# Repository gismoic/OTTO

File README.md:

# OTTO

A MP3 Player design I came up with about a year ago, the theroy behind it's design works as the following. The STM32C031C6T6 would interface the SD card through an SPI, stream Encodded audio data to the microcontroller, there it would be decoded into PCM samples, those samples would then be streamed to the LM49450, there it would be converted into analog audio signals which will be sent to speakers.

This project has no real hardware prototype but the design is here and can be revised if I ever feel like returning to this project. The firmware folder holds a software prototype for MP3 decodeding. A project that has proven to be very difficult. I would like to come back to this project in the future and come at with some new ideas. However, due to the fact that testing hardware like this would be very costly and difficult for me at the moment, I can not continue this project, but all the project files are in this repository for better storage in the future.

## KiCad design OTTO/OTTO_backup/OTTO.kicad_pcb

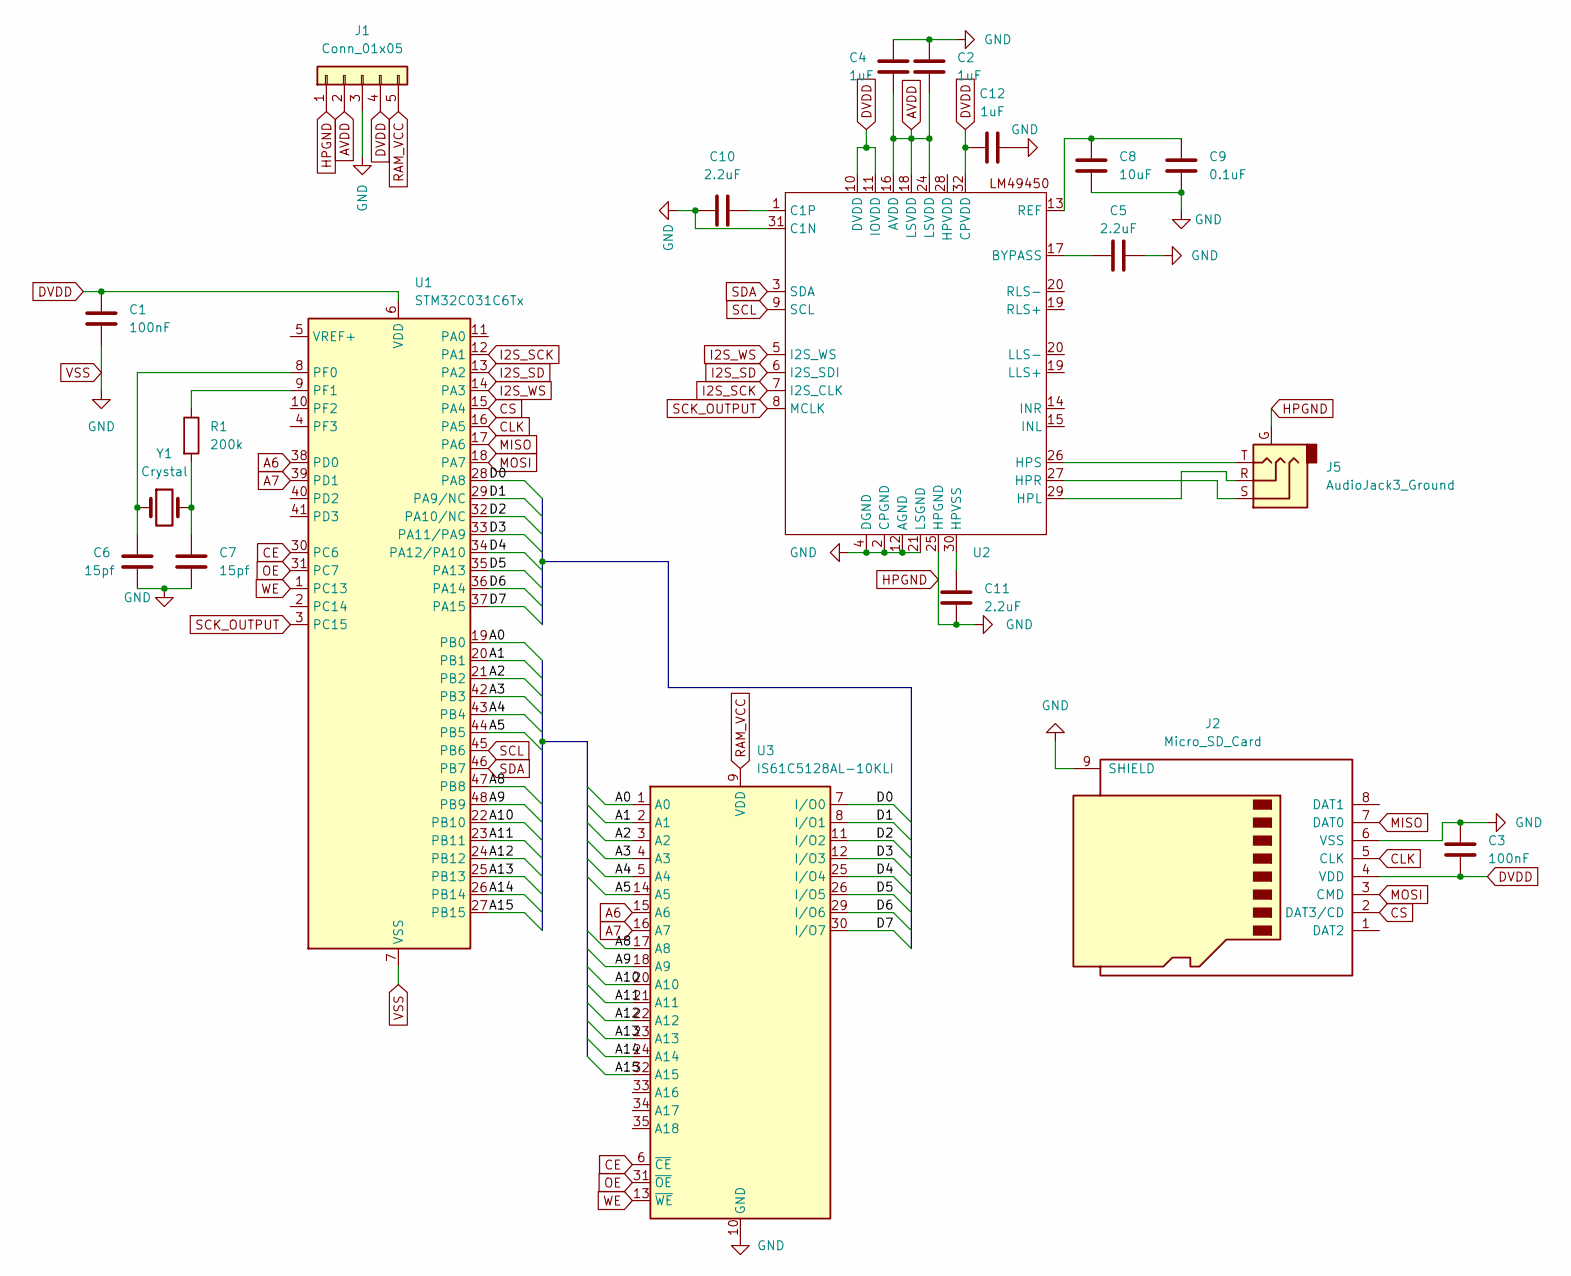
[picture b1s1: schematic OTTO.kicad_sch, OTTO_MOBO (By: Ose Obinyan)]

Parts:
C1, C3: 100nF; C_0201_0603Metric_Pad0.64x0.40mm_HandSolder
C2, C4, C12: 1uF; C_0201_0603Metric_Pad0.64x0.40mm_HandSolder
C5, C10, C11: 2.2uF; C_0201_0603Metric_Pad0.64x0.40mm_HandSolder
C6, C7: 15pf; C_0201_0603Metric_Pad0.64x0.40mm_HandSolder
C8: 10uF; C_0201_0603Metric_Pad0.64x0.40mm_HandSolder
C9: 0.1uF; C_0201_0603Metric_Pad0.64x0.40mm_HandSolder
J1: Conn_01x05; PinHeader_1x05_P1.00mm_Vertical
J2: Micro_SD_Card; microSD_HC_Hirose_DM3D-SF
J5: AudioJack3_Ground; Jack_3.5mm_CUI_SJ2-3593D-SMT_Horizontal
R1: 200k; R_0201_0603Metric_Pad0.64x0.40mm_HandSolder
U1: STM32C031C6Tx; LQFP-48_7x7mm_P0.5mm
U2: WQFN-32-1EP_5x5mm_P0.5mm_EP3.1x3.1mm
U3: IS61C5128AL-10KLI; SOJ-36_10.16x23.49mm_P1.27mm
Y1: Crystal; Crystal_SMD_EuroQuartz_MJ-4Pin_5.0x3.2mm_HandSoldering

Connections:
/A0: U1.19 (PB0), U3.1 (A0)
/A1: U1.20 (PB1), U3.2 (A1)
/A2: U1.21 (PB2), U3.3 (A2)
/A3: U1.42 (PB3), U3.4 (A3)
/A4: U1.43 (PB4), U3.5 (A4)
/A5: U1.44 (PB5), U3.14 (A5)
/A8: U1.47 (PB8), U3.17 (A8)
/A9: U1.48 (PB9), U3.18 (A9)
/A10: U1.22 (PB10), U3.20 (A10)
/A11: U1.23 (PB11), U3.21 (A11)
/A12: U1.24 (PB12), U3.22 (A12)
/A13: U1.25 (PB13), U3.23 (A13)
/A14: U1.26 (PB14), U3.24 (A14)
/A15: U1.27 (PB15), U3.32 (A15)
/D0: U1.28 (PA8), U3.7 (I/O0)
/D1: U1.29 (PA9/NC), U3.8 (I/O1)
/D2: U1.32 (PA10/NC), U3.11 (I/O2)
/D3: U1.33 (PA11/PA9), U3.12 (I/O3)
/D4: U1.34 (PA12/PA10), U3.25 (I/O4)
/D5: U1.35 (PA13), U3.26 (I/O5)
/D6: U1.36 (PA14), U3.29 (I/O6)
/D7: U1.37 (PA15), U3.30 (I/O7)
A6: U1.38 (PD0), U3.15 (A6)
A7: U1.39 (PD1), U3.16 (A7)
AVDD: C2.2, C4.2, J1.2, U2.16 (AVDD), U2.18 (LSVDD), U2.24 (LSVDD)
CE: U1.30 (PC6), U3.6 (~CE)
CLK: J2.5 (CLK), U1.16 (PA5)
CS: J2.2 (DAT3/CD), U1.15 (PA4)
DVDD: C1.1, C3.2, C12.1, J1.4, J2.4 (VDD), U1.6 (VDD), U2.10 (DVDD), U2.11 (IOVDD), U2.32 (CPVDD)
HPGND: C1.2, C2.1, C3.1, C4.1, C5.2, C6.2, C7.2, C8.1, C9.1, C10.1, C11.1, C12.2, J1.1, J1.3, J2.6 (VSS), J2.9 (SHIELD), J5.G, U1.7 (VSS), U2.2 (CPGND), U2.4 (DGND), U2.12 (AGND), U2.21 (LSGND), U2.25 (HPGND), U2.31 (C1N), U3.10 (GND), U3.28 (GND)
I2S_SCK: U1.12 (PA1), U2.7 (I2S_CLK)
I2S_SD: U1.13 (PA2), U2.6 (I2S_SDI)
I2S_WS: U1.14 (PA3), U2.5 (I2S_WS)
MISO: J2.7 (DAT0), U1.17 (PA6)
MOSI: J2.3 (CMD), U1.18 (PA7)
unnamed: C7.1, R1.2, Y1.2
unnamed: C6.1, U1.8 (PF0), Y1.1
unnamed: R1.1, U1.9 (PF1)
unnamed: C5.1, U2.17 (BYPASS)
unnamed: C10.2, U2.1 (C1P)
unnamed: J5.R, U2.29 (HPL)
unnamed: J5.S, U2.27 (HPR)
unnamed: J5.T, U2.26 (HPS)
unnamed: C11.2, U2.30 (HPVSS)
unnamed: C8.2, C9.2, U2.13 (REF)
OE: U1.31 (PC7), U3.31 (~OE)
RAM_VCC: J1.5, U3.9 (VDD), U3.27 (VDD)
SCK_OUTPUT: U1.3 (PC15), U2.8 (MCLK)
SCL: U1.45 (PB6), U2.9 (SCL)
SDA: U1.46 (PB7), U2.3 (SDA)
WE: U1.1 (PC13), U3.13 (~WE)

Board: 2 copper layers, 20 parts (0 on the bottom side), 51 nets, no tracks yet.

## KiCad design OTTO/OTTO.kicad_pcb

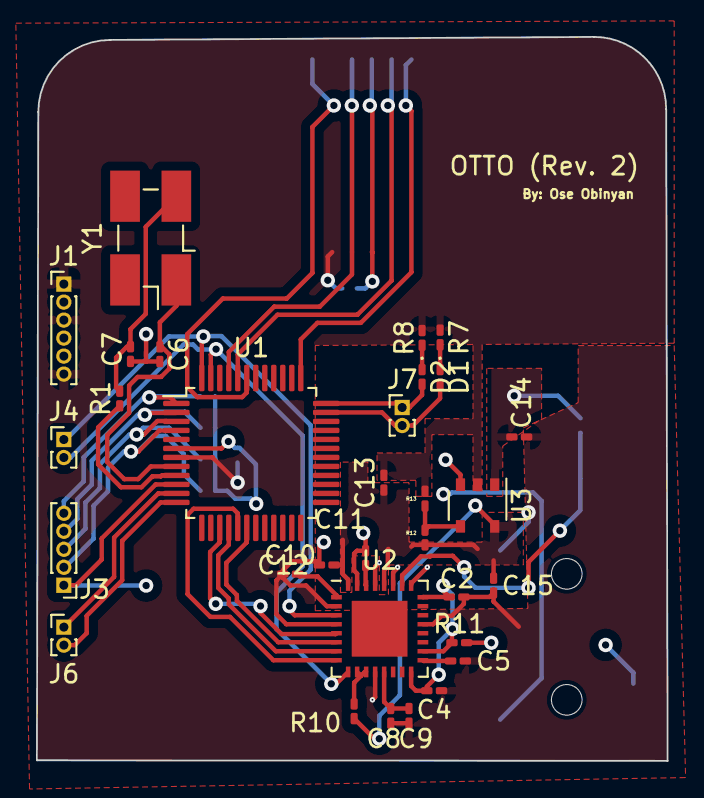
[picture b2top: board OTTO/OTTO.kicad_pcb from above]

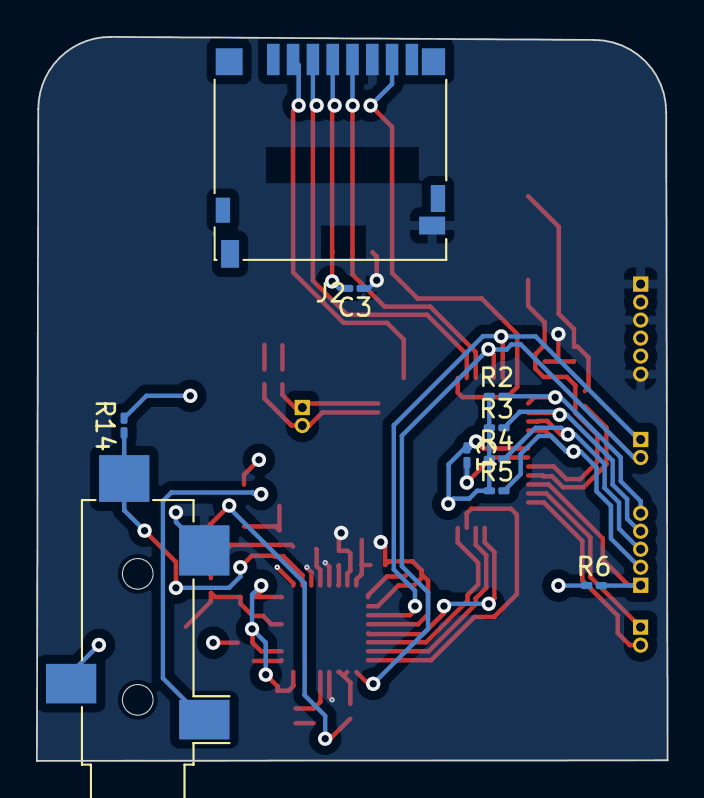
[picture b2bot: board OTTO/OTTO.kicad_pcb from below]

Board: 4 copper layers, 35.0 x 40.2 mm, 41 parts (10 on the bottom side), 37 nets.

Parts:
C1, C3: 100nF; C_0201_0603Metric_Pad0.64x0.40mm_HandSolder
C2, C4, C12, C13, C14: 1uF; C_0201_0603Metric_Pad0.64x0.40mm_HandSolder
C5, C10, C11: 2.2uF; C_0201_0603Metric_Pad0.64x0.40mm_HandSolder
C6, C7: 15pf; C_0201_0603Metric_Pad0.64x0.40mm_HandSolder
C8: 10uF; C_0201_0603Metric_Pad0.64x0.40mm_HandSolder
C9: 0.1uF; C_0201_0603Metric_Pad0.64x0.40mm_HandSolder
C15: 0.7uF; C_0201_0603Metric_Pad0.64x0.40mm_HandSolder
D1, D2: LED; LED_0201_0603Metric_Pad0.64x0.40mm_HandSolder
J1: Conn_01x05; PinHeader_1x06_P1.00mm_Vertical
J2: Micro_SD_Card; microSD_HC_Hirose_DM3D-SF
J3: Conn_01x05; PinHeader_1x05_P1.00mm_Vertical
J4, J6, J7: Conn_01x02; PinHeader_1x02_P1.00mm_Vertical
J5: AudioJack3_SwitchT; Jack_3.5mm_CUI_SJ-3524-SMT_Horizontal
R1: 200k; R_0201_0603Metric_Pad0.64x0.40mm_HandSolder
R2, R3, R4, R5, R6, R7, R8, R14: 1k; R_0201_0603Metric_Pad0.64x0.40mm_HandSolder
R10, R11: 300; R_0201_0603Metric_Pad0.64x0.40mm_HandSolder
R12: 500; R_0201_0603Metric_Pad0.64x0.40mm_HandSolder
R13: 357; R_0201_0603Metric_Pad0.64x0.40mm_HandSolder
U1: STM32C031C6Tx; LQFP-48_7x7mm_P0.5mm
U2: WQFN-32-1EP_5x5mm_P0.5mm_EP3.1x3.1mm
U3: TSOP-5_1.65x3.05mm_P0.95mm
Y1: Crystal; Crystal_SMD_EuroQuartz_MJ-4Pin_5.0x3.2mm_HandSoldering

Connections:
2.7v: C12.1, C13.1, C15.2, R10.2, R12.1, U2.28 (HPVDD), U2.32 (CPVDD), U3.5 (VOUT)
3.3v: C1.1, C3.2, C14.2, J1.4, J2.4 (VDD), R2.1, R3.1, R4.1, R5.1, R6.1, R11.2, R14.2, U1.6 (VDD), U3.1 (VIN), U3.3 (EN)
.: J3.5, R2.2, U1.1 (PC13)
..: J3.4, R3.2, U1.2 (PC14)
...: J3.3, R4.2, U1.3 (PC15)
....: J3.2, R5.2, U1.4 (PF3)
CLK: J2.5 (CLK), U1.45 (PB6)
CS: J2.2 (DAT3/CD), U1.37 (PA15)
Enter: J3.1, R6.2, U1.10 (PF2)
HPL: J5.S, U2.29 (HPL)
HPR: J5.R, U2.27 (HPR)
HPS: J5.TN, R14.1, U2.26 (HPS)
I2S_MCK: U1.17 (PA6), U2.8 (MCLK)
I2S_SCK: U1.16 (PA5), U2.7 (I2S_CLK)
I2S_SD: U1.18 (PA7), U2.6 (I2S_SDI)
I2S_WS: U1.15 (PA4), U2.5 (I2S_WS)
MISO: J2.7 (DAT0), U1.43 (PB4)
MOSI: J2.3 (CMD), U1.44 (PB5)
unnamed: C7.1, R1.2, Y1.2
unnamed: D1.1 (K), R7.2
unnamed: D2.1 (K), R8.2
unnamed: C6.1, U1.8 (PF0), Y1.1
unnamed: R1.1, U1.9 (PF1)
unnamed: C2.2, C4.2, R11.1, U2.16 (AVDD), U2.18 (LSVDD), U2.24 (LSVDD)
unnamed: C5.1, U2.17 (BYPASS)
unnamed: C10.2, U2.1 (C1P)
unnamed: R10.1, U2.10 (DVDD), U2.11 (IOVDD)
unnamed: C11.2, U2.30 (HPVSS)
unnamed: C8.2, C9.2, U2.13 (REF)
unnamed: R12.2, R13.1, U3.4 (ADJ)
RX: J6.2, U1.12 (PA1)
SCL: J4.2, U1.47 (PB8), U2.9 (SCL)
SDA: J4.1, U1.48 (PB9), U2.3 (SDA)
SWCLK: D2.2 (A), J7.1, U1.36 (PA14)
SWDIO: D1.2 (A), J7.2, U1.35 (PA13)
TX: J6.1, U1.11 (PA0)
VSS: C1.2, C2.1, C3.1, C4.1, C5.2, C6.2, C7.2, C8.1, C9.1, C10.1, C11.1, C12.2, C13.2, C14.1, C15.1, J1.1, J1.3, J1.6, J2.6 (VSS), J2.9 (SHIELD), J5.T, R7.1, R8.1, R13.2, U1.7 (VSS), U2.2 (CPGND), U2.4 (DGND), U2.12 (AGND), U2.21 (LSGND), U2.25 (HPGND), U2.31 (C1N), U3.2 (GND)

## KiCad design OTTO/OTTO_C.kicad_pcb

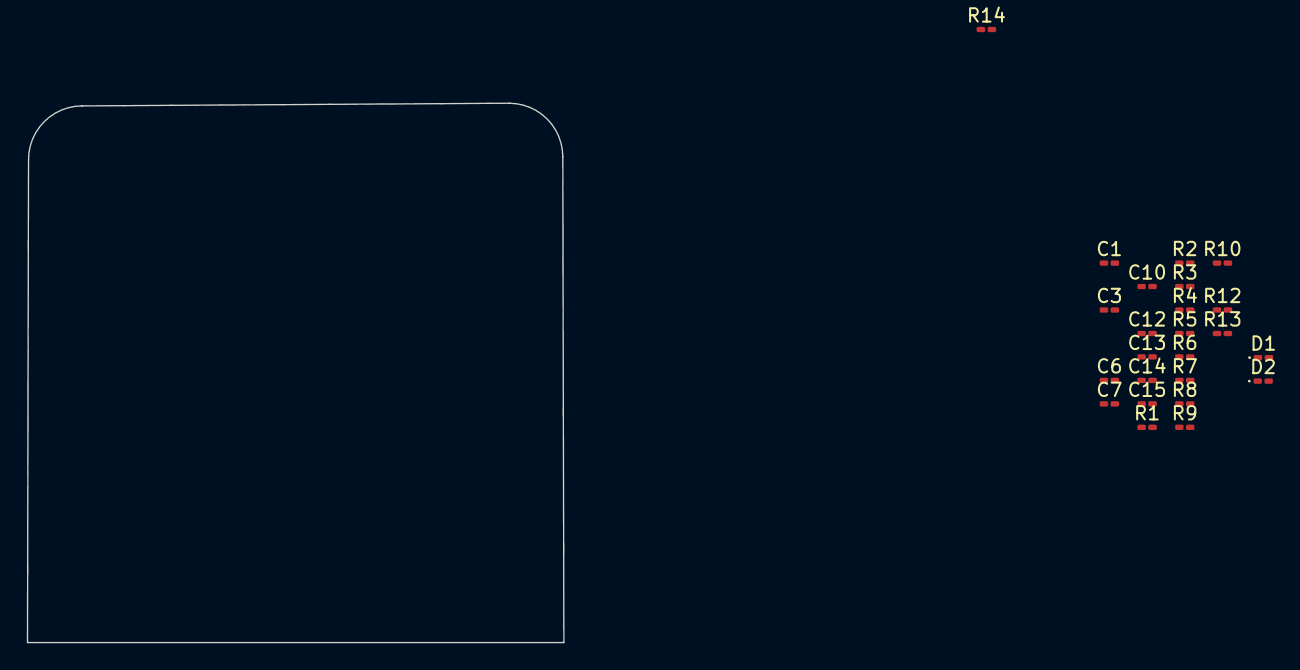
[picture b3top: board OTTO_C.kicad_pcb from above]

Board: 2 copper layers, 40.0 x 40.2 mm, 24 parts (0 on the bottom side), 7 nets, no tracks yet.

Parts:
C1, C3: 100nF; C_0201_0603Metric_Pad0.64x0.40mm_HandSolder
C6, C7: 15pf; C_0201_0603Metric_Pad0.64x0.40mm_HandSolder
C10: 2.2uF; C_0201_0603Metric_Pad0.64x0.40mm_HandSolder
C12, C13, C14: 1uF; C_0201_0603Metric_Pad0.64x0.40mm_HandSolder
C15: 0.7uF; C_0201_0603Metric_Pad0.64x0.40mm_HandSolder
D1, D2: LED; LED_0201_0603Metric_Pad0.64x0.40mm_HandSolder
R1: 200k; R_0201_0603Metric_Pad0.64x0.40mm_HandSolder
R2, R3, R4, R5, R6, R7, R8, R14: 1k; R_0201_0603Metric_Pad0.64x0.40mm_HandSolder
R9: 47; R_0201_0603Metric_Pad0.64x0.40mm_HandSolder
R10: 300; R_0201_0603Metric_Pad0.64x0.40mm_HandSolder
R12: 500; R_0201_0603Metric_Pad0.64x0.40mm_HandSolder
R13: 357; R_0201_0603Metric_Pad0.64x0.40mm_HandSolder

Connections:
2.7v: C12.1, C13.1, C15.2, R10.2, R12.1
3.3v: C1.1, C3.2, C14.2, R2.1, R3.1, R4.1, R5.1, R6.1, R9.1, R14.2
unnamed: C7.1, R1.2
unnamed: D1.1 (K), R7.2
unnamed: D2.1 (K), R8.2
unnamed: R12.2, R13.1
VSS: C1.2, C3.1, C6.2, C7.2, C10.1, C12.2, C13.2, C14.1, C15.1, R7.1, R8.1, R13.2

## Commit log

2025-01-03 Create desc
2025-01-03 Create tmp
